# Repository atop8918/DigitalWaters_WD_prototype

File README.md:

# DigitalWaters_WD_prototype
Simplified Schematic for prototype release

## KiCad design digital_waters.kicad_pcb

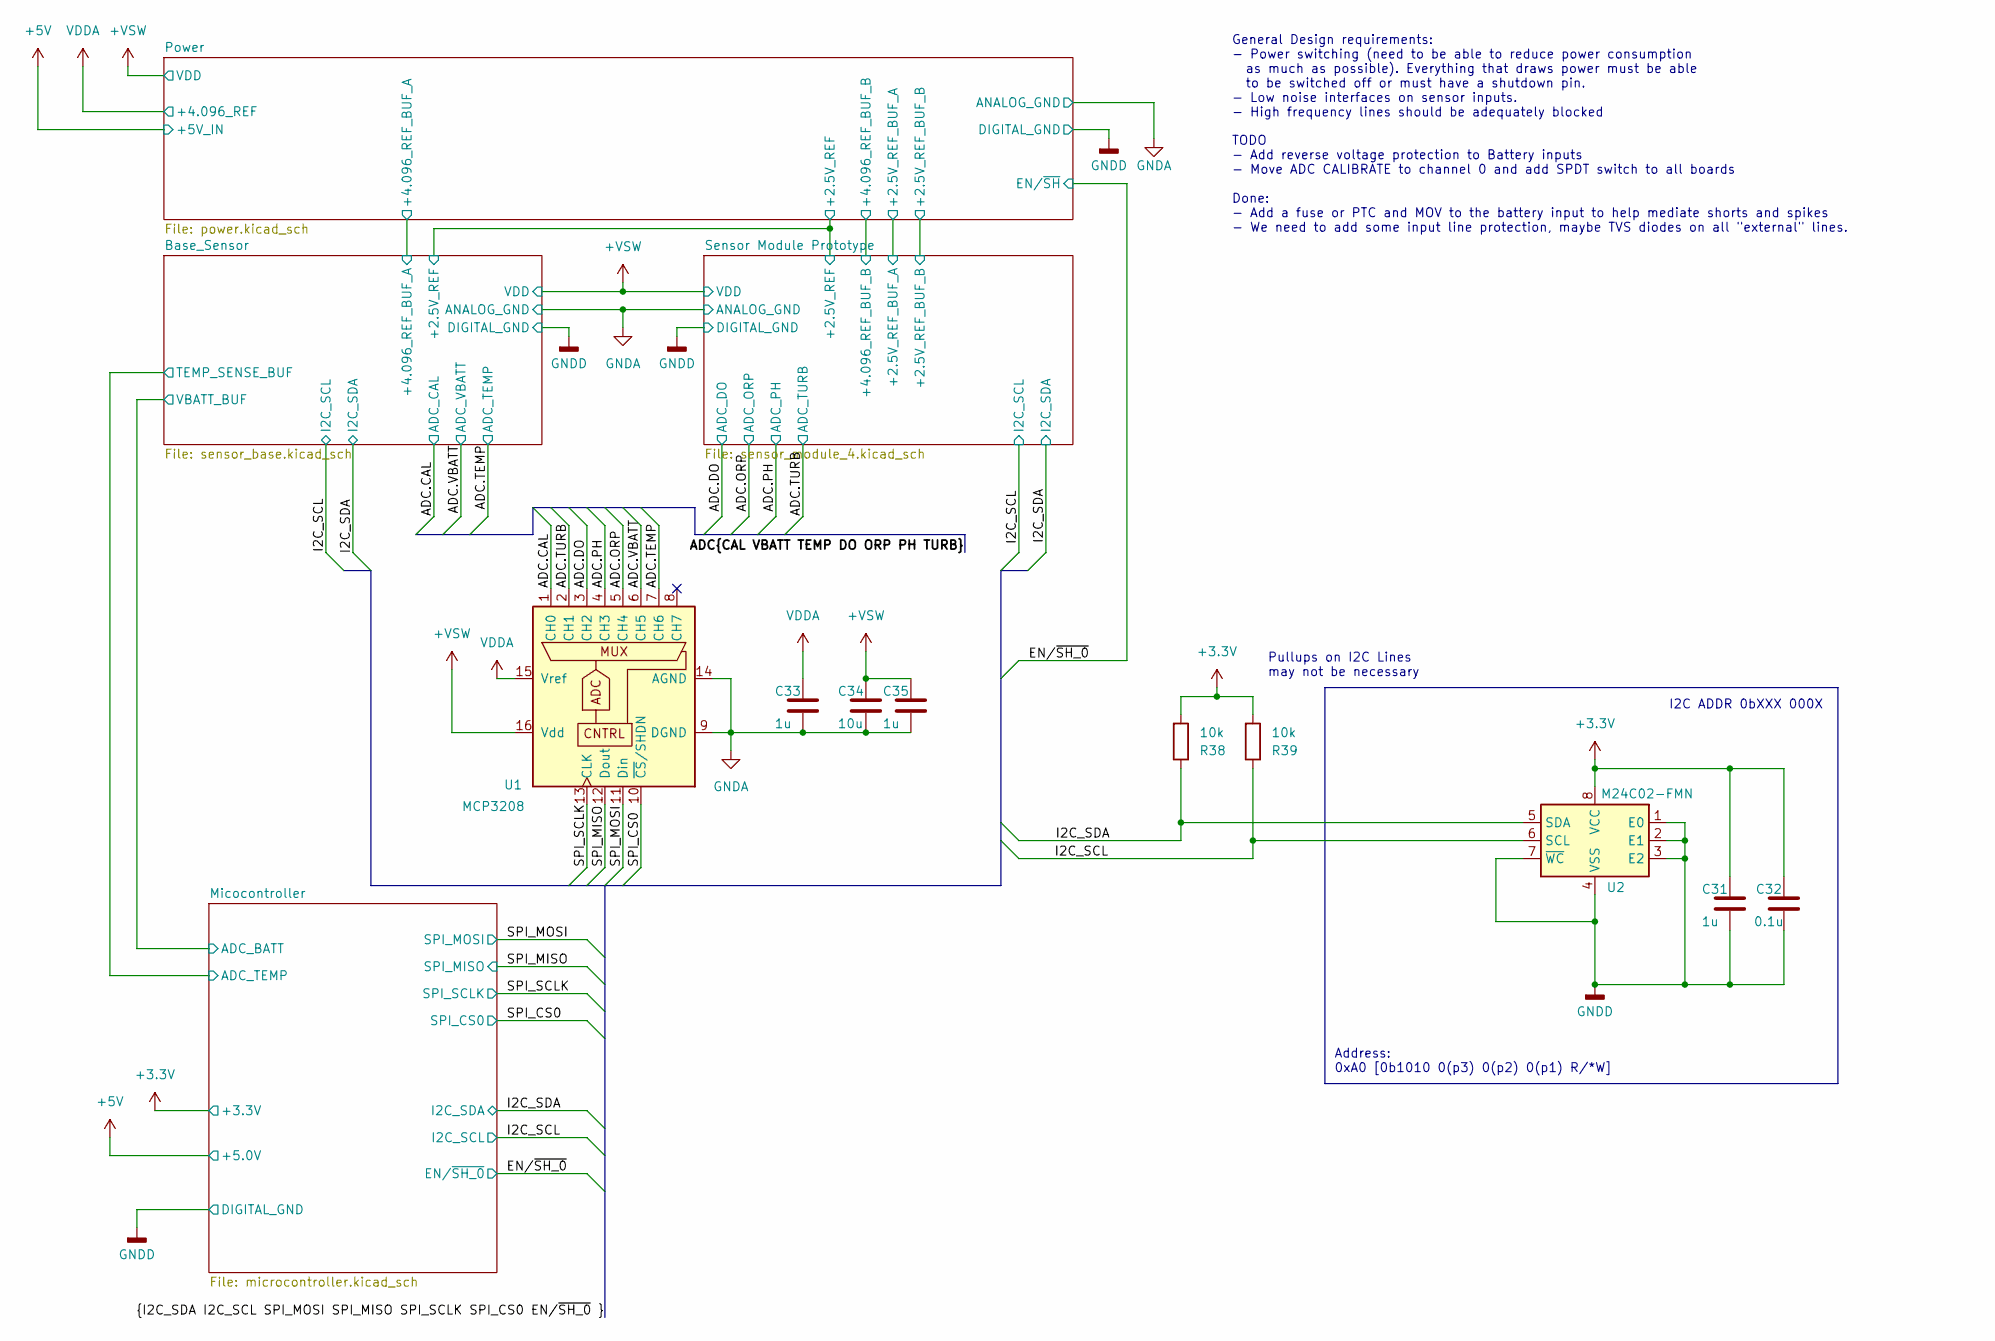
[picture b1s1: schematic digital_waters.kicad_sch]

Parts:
C31, C33, C35: 1u; C_1210_3225Metric_Pad1.33x2.70mm_HandSolder
C32: 0.1u; C_1210_3225Metric_Pad1.33x2.70mm_HandSolder
C34: 10u; C_1210_3225Metric_Pad1.33x2.70mm_HandSolder
R38, R39: 10k; R_1210_3225Metric_Pad1.30x2.65mm_HandSolder
U1: MCP3208; SOIC-16_3.9x9.9mm_P1.27mm
U2: M24C02-FMN; SOIC-8_3.9x4.9mm_P1.27mm

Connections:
+3.3V: C31.1, C32.1, R38.2, R39.2, U2.8 (VCC); also elsewhere on the board
+VSW: C34.1, C35.1, U1.16 (Vdd); also elsewhere on the board
/ADC.CAL: U1.1 (CH0); also elsewhere on the board
/ADC.DO: U1.3 (CH2); also elsewhere on the board
/ADC.ORP: U1.5 (CH4); also elsewhere on the board
/ADC.PH: U1.4 (CH3); also elsewhere on the board
/ADC.TEMP: U1.7 (CH6); also elsewhere on the board
/ADC.TURB: U1.2 (CH1); also elsewhere on the board
/ADC.VBATT: U1.6 (CH5); also elsewhere on the board
/I2C_SCL: R39.1, U2.6 (SCL); also elsewhere on the board
/I2C_SDA: R38.1, U2.5 (SDA); also elsewhere on the board
/SPI_CS0: U1.10 (~CS/SHDN); also elsewhere on the board
/SPI_MISO: U1.12 (Dout); also elsewhere on the board
/SPI_MOSI: U1.11 (Din); also elsewhere on the board
/SPI_SCLK: U1.13 (CLK); also elsewhere on the board
GNDA: C33.2, C34.2, C35.2, U1.9 (DGND), U1.14 (AGND); also elsewhere on the board
GNDD: C31.2, C32.2, U2.1 (E0), U2.2 (E1), U2.3 (E2), U2.4 (VSS), U2.7 (~WC); also elsewhere on the board
VDDA: C33.1, U1.15 (Vref); also elsewhere on the board

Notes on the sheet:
I2C ADDR 0bXXX 000X
Address: 0xA0 [0b1010 0(p3) 0(p2) 0(p1) R/*W]
TODO - Add reverse voltage protection to Battery inputs - Move ADC CALIBRATE to channel 0 and add SPDT switch to all boards Done: - Add a fuse or PTC and MOV to the battery input to help mediate shorts and spikes - We need to add some input line protection, maybe TVS diodes on all "external" lines.
Pullups on I2C Lines may not be necessary
General Design requirements: - Power switching (need to be able to reduce power consumption as much as possible). Everything that draws power must be able to be switched off or must have a shutdown pin. - Low noise interfaces on sensor inputs. - High frequency lines should be adequately blocked

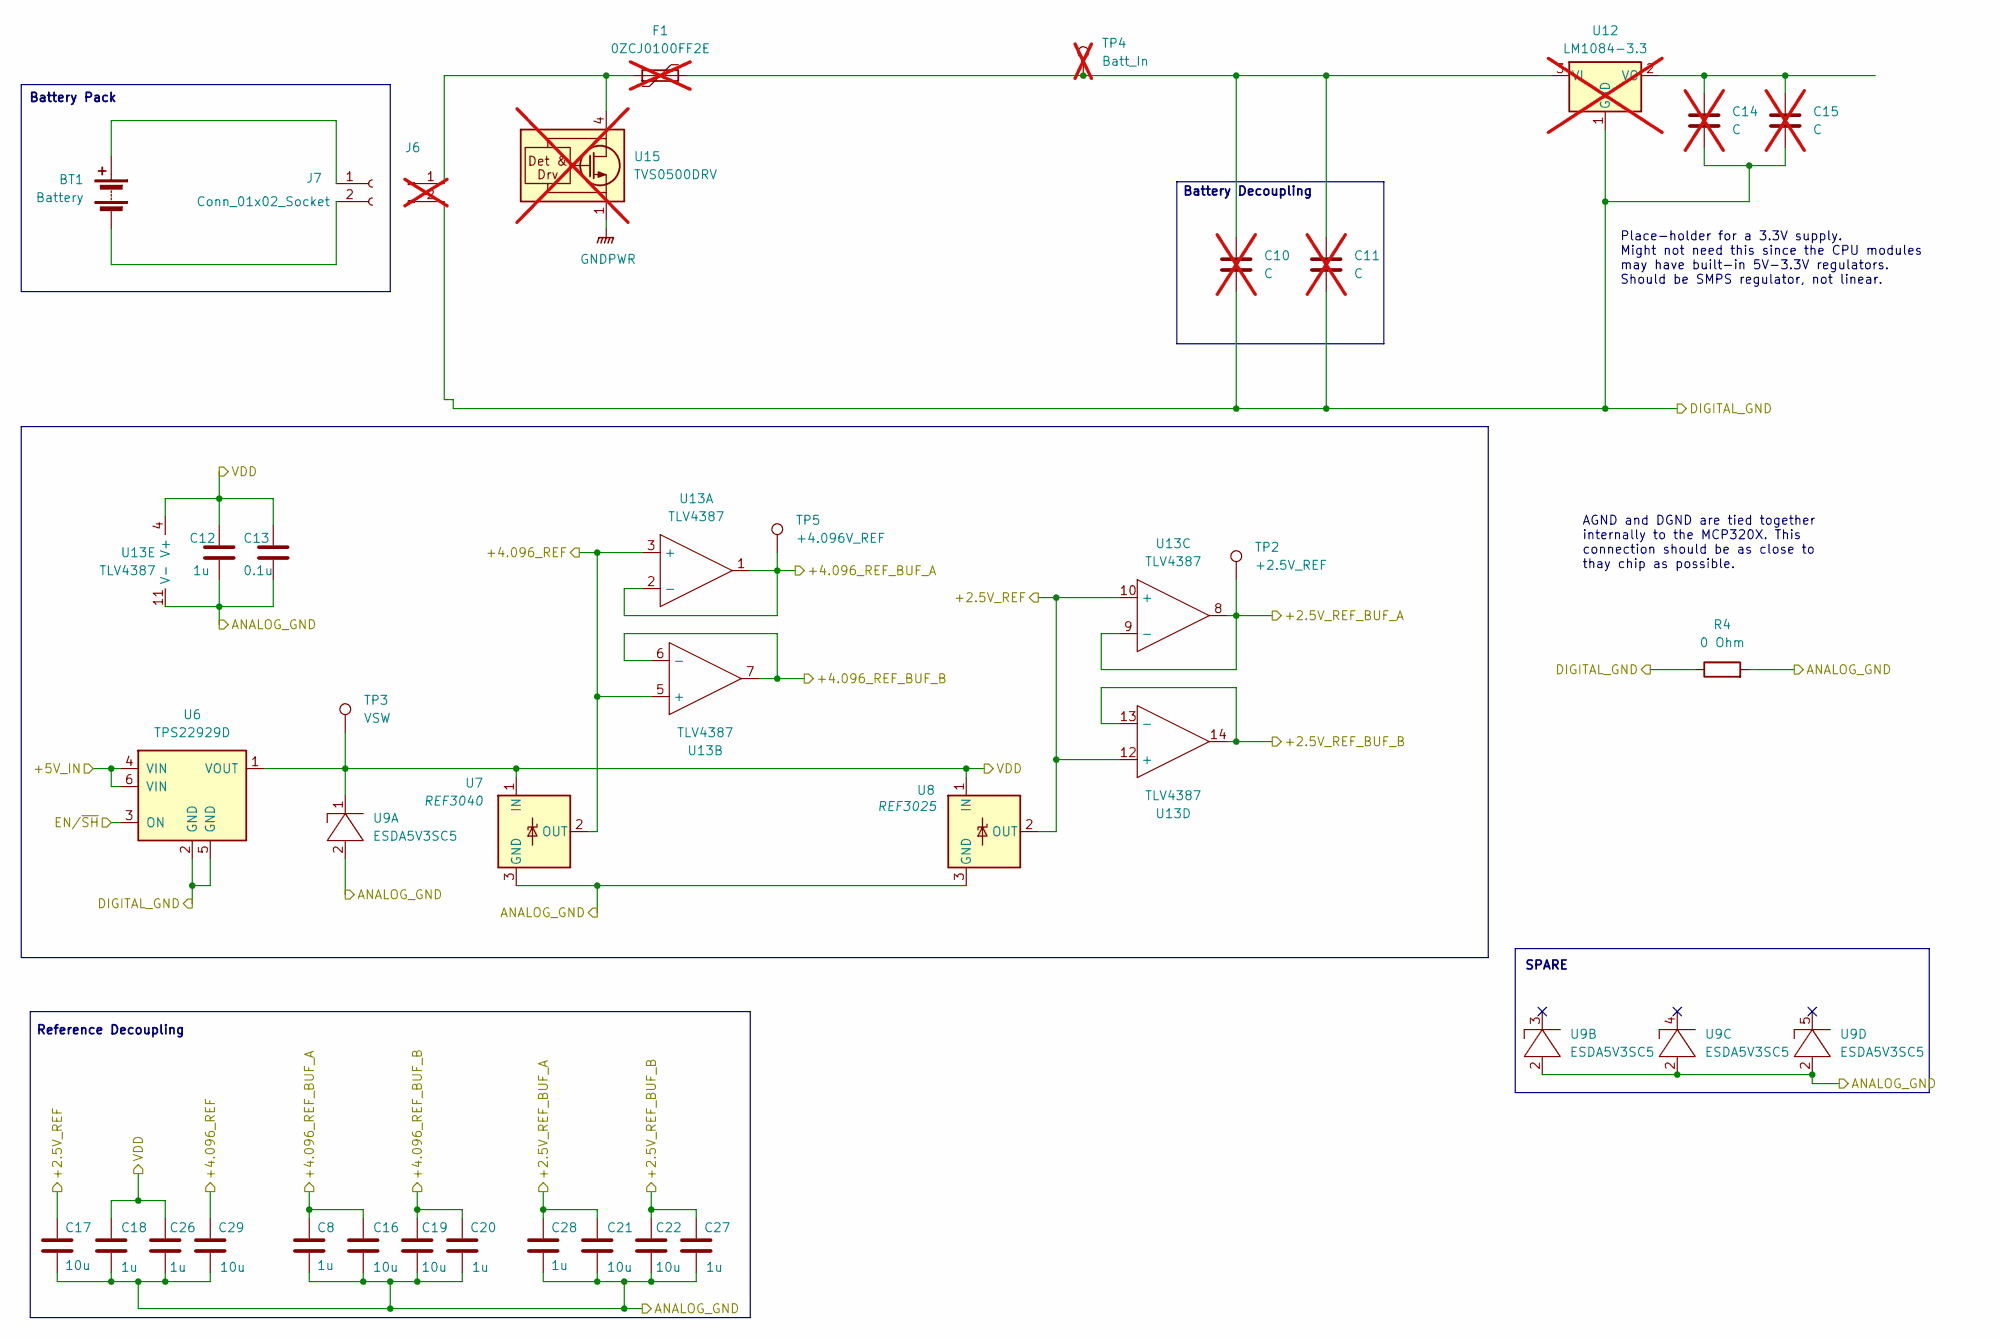
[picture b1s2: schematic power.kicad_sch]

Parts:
BT1: Battery
C8, C12, C18, C20, C26, C27, C28: 1u; C_1210_3225Metric_Pad1.33x2.70mm_HandSolder
C10, C11, C14, C15: C; C_1210_3225Metric_Pad1.33x2.70mm_HandSolder; not fitted
C13: 0.1u; C_1210_3225Metric_Pad1.33x2.70mm_HandSolder
C16, C17, C19, C21, C22, C29: 10u; C_1210_3225Metric_Pad1.33x2.70mm_HandSolder
F1: 0ZCJ0100FF2E; Fuse_1206_3216Metric_Pad1.42x1.75mm_HandSolder; not fitted
J6: Battery In; PinHeader_1x02_P2.54mm_Vertical_SMD_Pin1Left; not fitted
J7: Conn_01x02_Socket
R4: 0 Ohm; R_1210_3225Metric_Pad1.30x2.65mm_HandSolder
TP2: +2.5V_REF; TestPoint_Pad_D3.0mm
TP3: VSW; TestPoint_Pad_D3.0mm
TP4: Batt_In; TestPoint_Pad_D3.0mm; not fitted
TP5: +4.096V_REF; TestPoint_Pad_D3.0mm
U6: TPS22929D; SOT-23-6
U7: REF3040; SOT-23
U8: REF3025; SOT-23
U9: ESDA5V3SC5; SOT-23-5
U12: LM1084-3.3; PinHeader_2x10_P2.54mm_Vertical_SMD; not fitted
U13: TLV4387; TSSOP-14_4.4x5mm_P0.65mm
U15: TVS0500DRV; WSON-6-1EP_2x2mm_P0.65mm_EP1x1.6mm; not fitted

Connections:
+5V: U6.4 (VIN), U6.6 (VIN); also elsewhere on the board
+VSW: C12.1, C13.1, C18.1, C26.1, TP3.1, U6.1 (VOUT), U7.1 (IN), U8.1 (IN), U9.1, U13.4 (V+); also elsewhere on the board
/Base_Sensor/+2.5V_REF: C17.1, U8.2 (OUT), U13.10 (+), U13.12 (+); also elsewhere on the board
/Base_Sensor/+4.096_REF_BUF_A: C8.1, C16.1, TP5.1, U13.1, U13.2 (-); also elsewhere on the board
/EN/~SH_0: U6.3 (ON); also elsewhere on the board
/Power/+2.5V_REF_BUF_A: C21.1, C28.1, TP2.1, U13.8, U13.9 (-); also elsewhere on the board
/Power/+2.5V_REF_BUF_B: C22.1, C27.1, U13.13 (-), U13.14; also elsewhere on the board
/Power/+4.096_REF_BUF_B: C19.1, C20.1, U13.6 (-), U13.7; also elsewhere on the board
GNDA: C8.2, C12.2, C13.2, C16.2, C17.2, C18.2, C19.2, C20.2, C21.2, C22.2, C26.2, C27.2, C28.2, C29.2, R4.2, U7.3 (GND), U8.3 (GND), U9.2, U13.11 (V-); also elsewhere on the board
GNDD: C10.2, C11.2, C14.2, C15.2, J6.2, R4.1, U6.2 (GND), U6.5 (GND), U12.1 (GND); also elsewhere on the board
unnamed: BT1.1 (+), J7.1
unnamed: BT1.2 (-), J7.2
unnamed: C10.1, C11.1, F1.2, TP4.1, U12.3 (VI)
unnamed: C14.1, C15.1, U12.2 (VO)
unnamed: F1.1, J6.1, U15.4 (IN), U15.5 (IN), U15.6 (IN)
unnamed: U15.1 (GND), U15.2 (GND), U15.3 (GND), U15.7 (GND)
VDDA: C29.1, U7.2 (OUT), U13.3 (+), U13.5 (+); also elsewhere on the board

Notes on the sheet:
Battery Pack
Place-holder for a 3.3V supply. Might not need this since the CPU modules may have built-in 5V-3.3V regulators. Should be SMPS regulator, not linear.
Battery Decoupling
AGND and DGND are tied together internally to the MCP320X. This connection should be as close to thay chip as possible.
SPARE
Reference Decoupling

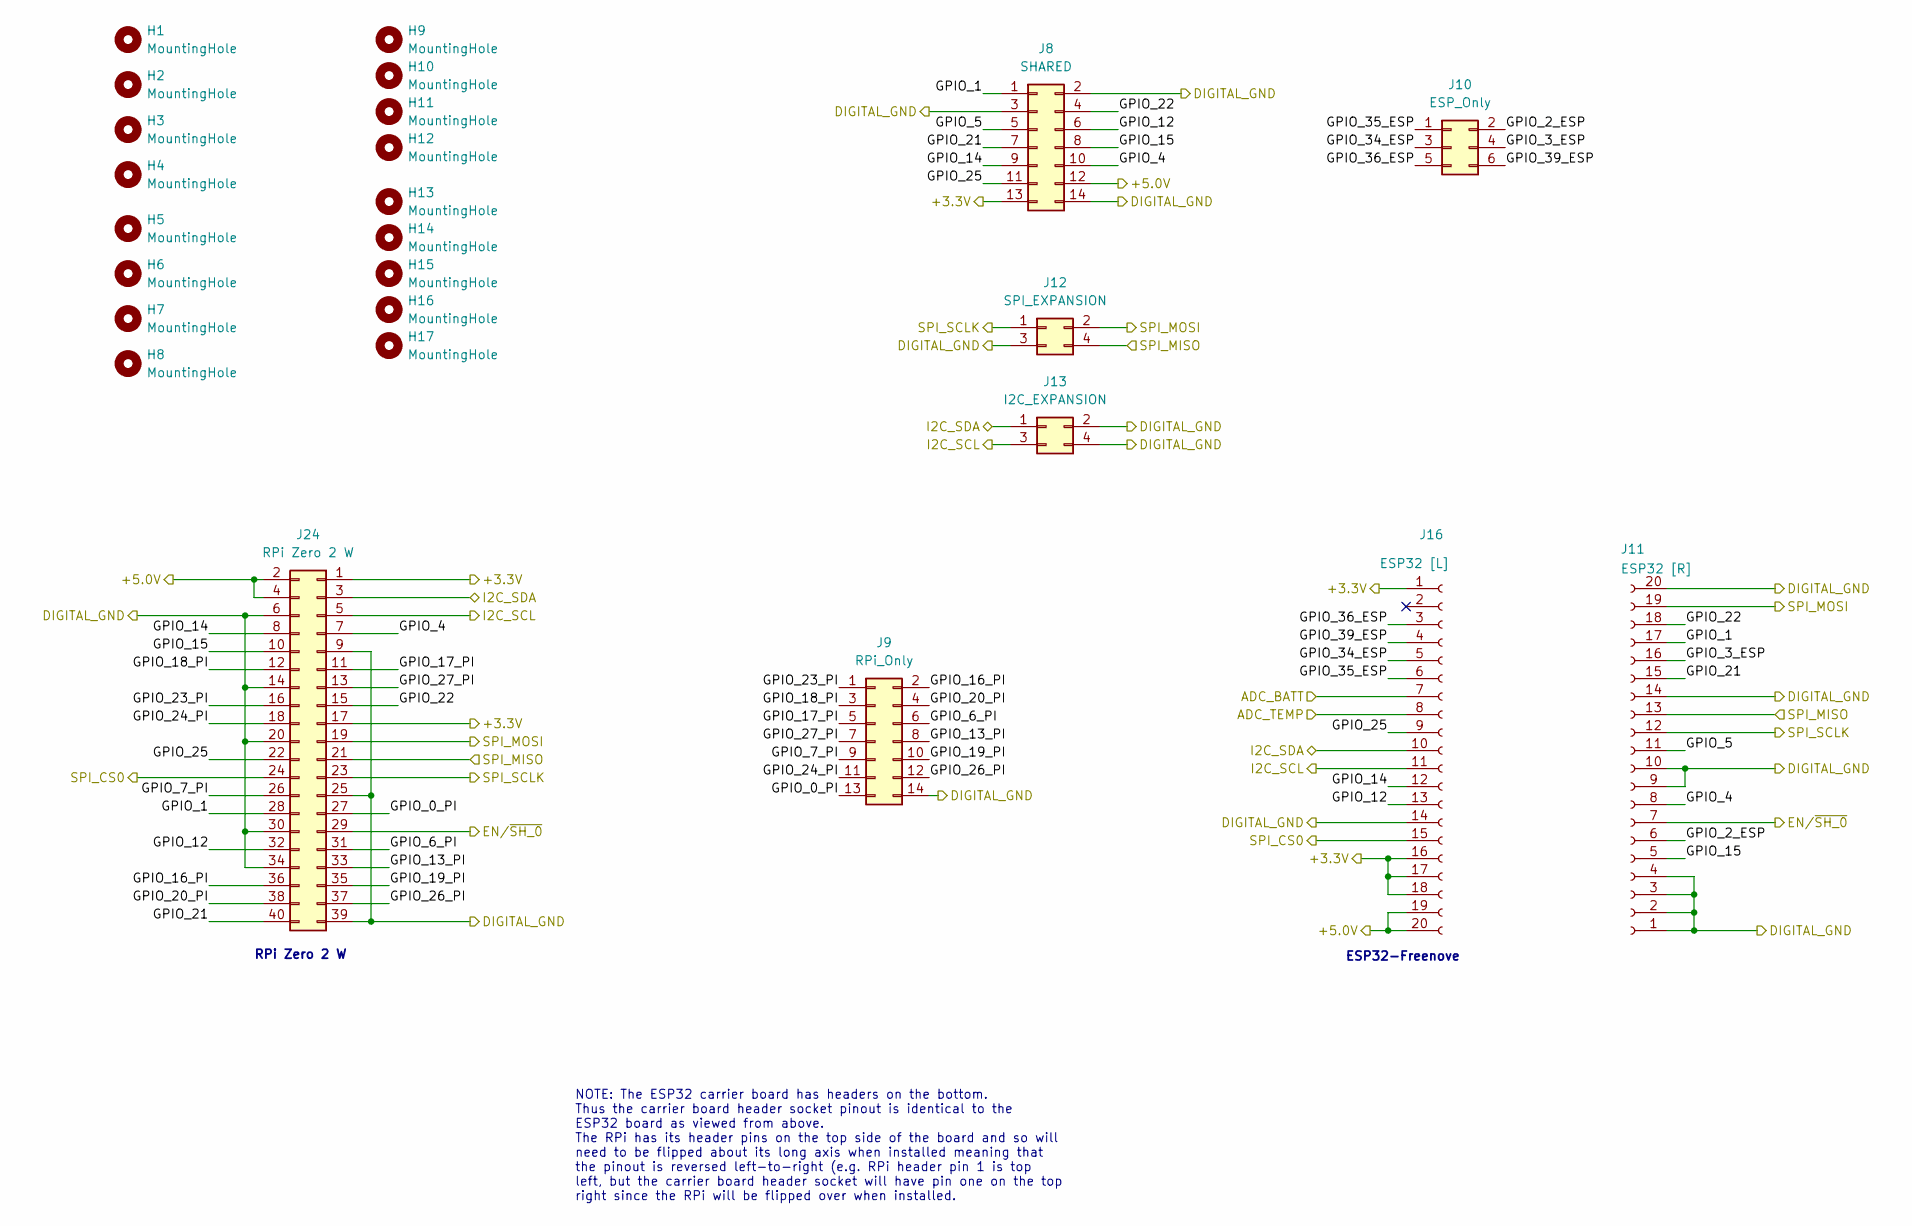
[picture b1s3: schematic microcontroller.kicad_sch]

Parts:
H1, H2, H3, H4, H5, H6, H7, H8, H9, H10, H11, H12, H13, H14, H15, H16, H17: MountingHole; MountingHole_2.7mm_M2.5_ISO14580
J8: SHARED; PinHeader_2x07_P2.54mm_Vertical_SMD
J9: RPi_Only; PinHeader_2x07_P2.54mm_Vertical_SMD
J10: ESP_Only; PinHeader_2x03_P2.54mm_Vertical_SMD
J11: ESP32 [R]; PinSocket_1x20_P2.54mm_Vertical_SMD_Pin1Left
J12: SPI_EXPANSION; PinHeader_2x02_P2.54mm_Vertical_SMD
J13: I2C_EXPANSION; PinHeader_2x02_P2.54mm_Vertical_SMD
J16: ESP32 [L]; PinSocket_1x20_P2.54mm_Vertical_SMD_Pin1Left
J24: RPi Zero 2 W; PinSocket_2x20_P2.54mm_Vertical_SMD

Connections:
+3.3V: J8.13, J16.1, J16.16, J16.17, J16.18, J24.1, J24.17; also elsewhere on the board
+5V: J8.12, J16.19, J16.20, J24.2, J24.4; also elsewhere on the board
/Base_Sensor/TEMP_SENSE_BUF: J16.8; also elsewhere on the board
/Base_Sensor/VBATT_BUF: J16.7; also elsewhere on the board
/EN/~SH_0: J11.7, J24.29; also elsewhere on the board
/I2C_SCL: J13.3, J16.11, J24.5; also elsewhere on the board
/I2C_SDA: J13.1, J16.10, J24.3; also elsewhere on the board
/Micocontroller/GPIO_0_PI: J9.13, J24.27
/Micocontroller/GPIO_1: J8.1, J11.17, J24.28
/Micocontroller/GPIO_2_ESP: J10.2, J11.6
/Micocontroller/GPIO_3_ESP: J10.4, J11.16
/Micocontroller/GPIO_4: J8.10, J11.8, J24.7
/Micocontroller/GPIO_5: J8.5, J11.11
/Micocontroller/GPIO_6_PI: J9.6, J24.31
/Micocontroller/GPIO_7_PI: J9.9, J24.26
/Micocontroller/GPIO_12: J8.6, J16.13, J24.32
/Micocontroller/GPIO_13_PI: J9.8, J24.33
/Micocontroller/GPIO_14: J8.9, J16.12, J24.8
/Micocontroller/GPIO_15: J8.8, J11.5, J24.10
/Micocontroller/GPIO_16_PI: J9.2, J24.36
/Micocontroller/GPIO_17_PI: J9.5, J24.11
/Micocontroller/GPIO_18_PI: J9.3, J24.12
/Micocontroller/GPIO_19_PI: J9.10, J24.35
/Micocontroller/GPIO_20_PI: J9.4, J24.38
/Micocontroller/GPIO_21: J8.7, J11.15, J24.40
/Micocontroller/GPIO_22: J8.4, J11.18, J24.15
/Micocontroller/GPIO_23_PI: J9.1, J24.16
/Micocontroller/GPIO_24_PI: J9.11, J24.18
/Micocontroller/GPIO_25: J8.11, J16.9, J24.22
/Micocontroller/GPIO_26_PI: J9.12, J24.37
/Micocontroller/GPIO_27_PI: J9.7, J24.13
/Micocontroller/GPIO_34_ESP: J10.3, J16.5
/Micocontroller/GPIO_35_ESP: J10.1, J16.6
/Micocontroller/GPIO_36_ESP: J10.5, J16.3
/Micocontroller/GPIO_39_ESP: J10.6, J16.4
/SPI_CS0: J16.15, J24.24; also elsewhere on the board
/SPI_MISO: J11.13, J12.4, J24.21; also elsewhere on the board
/SPI_MOSI: J11.19, J12.2, J24.19; also elsewhere on the board
/SPI_SCLK: J11.12, J12.1, J24.23; also elsewhere on the board
GNDD: J8.2, J8.3, J8.14, J9.14, J11.1, J11.2, J11.3, J11.4, J11.9, J11.10, J11.14, J11.20, J12.3, J13.2, J13.4, J16.14, J24.6, J24.9, J24.14, J24.20, J24.25, J24.30, J24.34, J24.39; also elsewhere on the board

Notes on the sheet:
ESP32-Freenove
RPi Zero 2 W
NOTE: The ESP32 carrier board has headers on the bottom. Thus the carrier board header socket pinout is identical to the ESP32 board as viewed from above. The RPi has its header pins on the top side of the board and so will need to be flipped about its long axis when installed meaning that the pino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

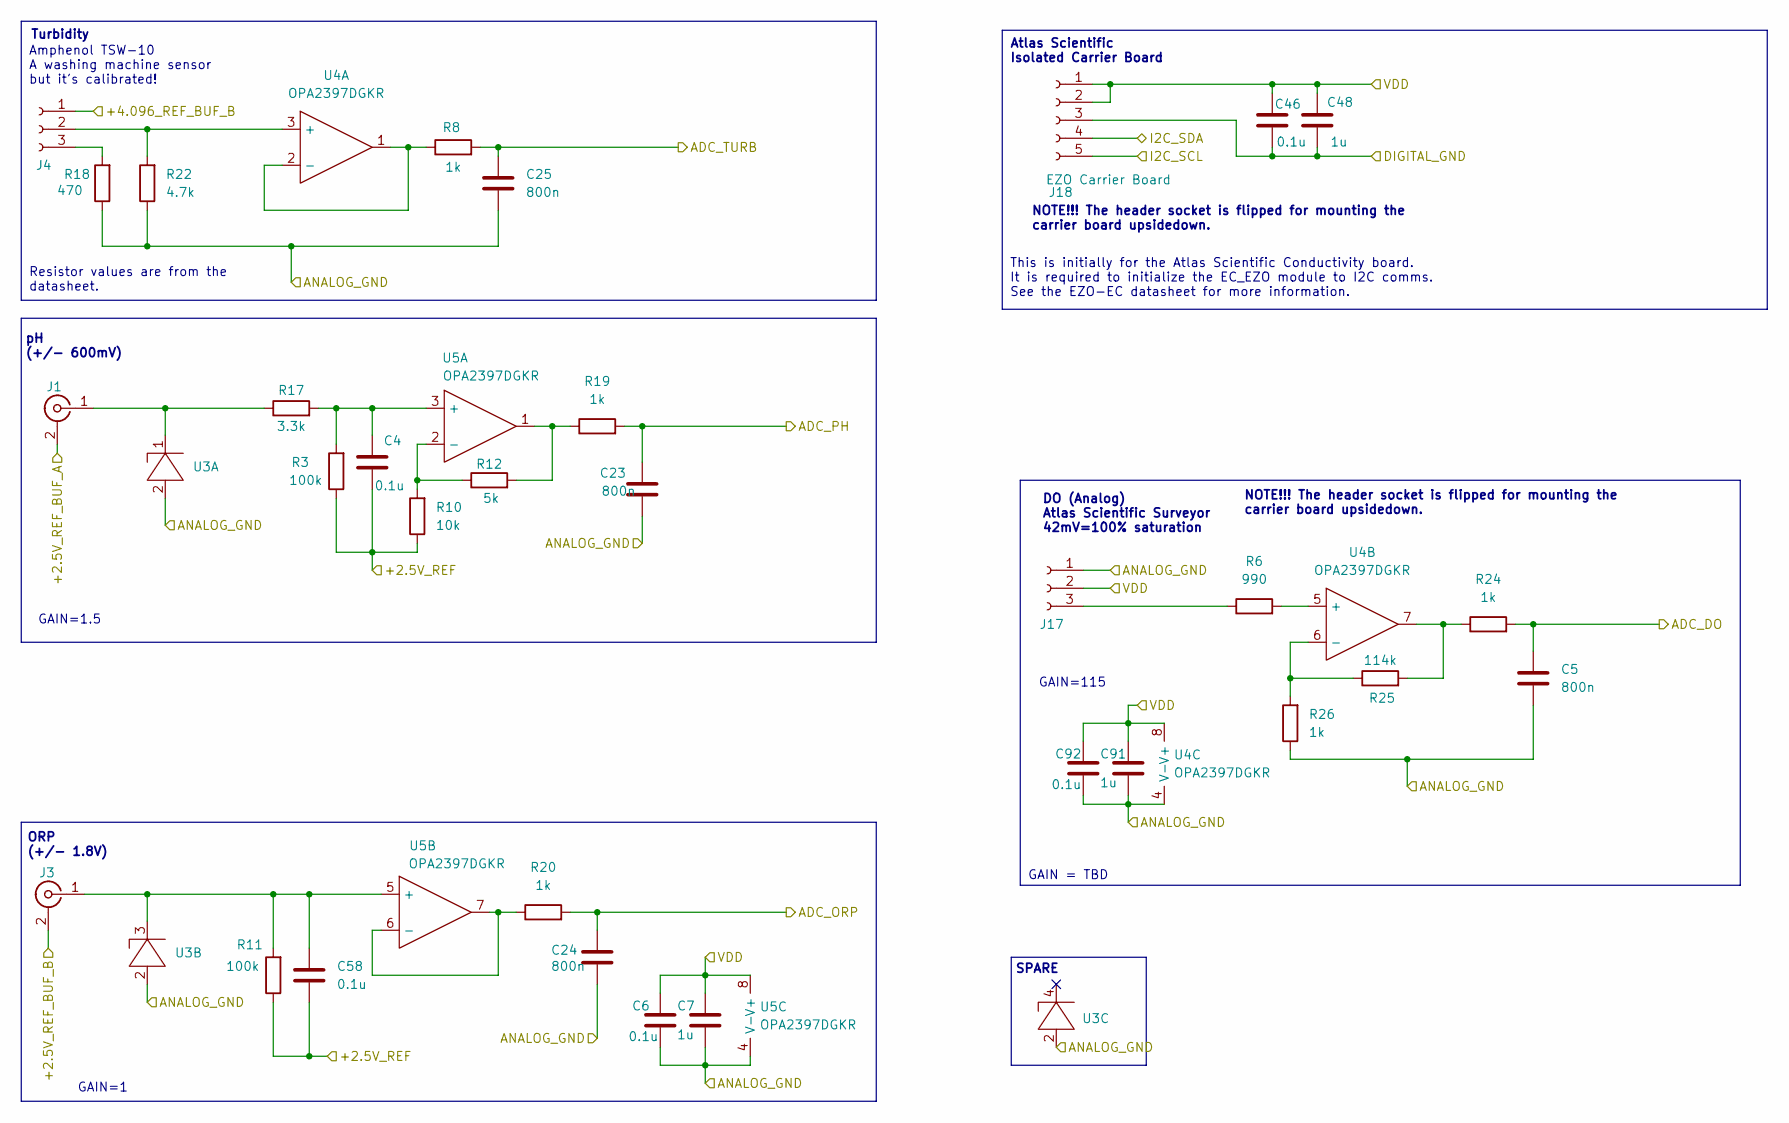
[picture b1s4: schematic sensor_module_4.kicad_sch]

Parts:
C4, C6, C46, C58, C92: 0.1u; C_1210_3225Metric_Pad1.33x2.70mm_HandSolder
C5, C23, C24, C25: 800n; C_1210_3225Metric_Pad1.33x2.70mm_HandSolder
C7, C48, C91: 1u; C_1210_3225Metric_Pad1.33x2.70mm_HandSolder
J1: pH_IN; PinHeader_1x02_P2.54mm_Vertical_SMD_Pin1Left
J3: ORP_In; PinHeader_1x02_P2.54mm_Vertical_SMD_Pin1Left
J4: Turbidity TSW-10; PinHeader_1x03_P2.54mm_Vertical_SMD_Pin1Left
J17: Atlas Surveyor; PinSocket_1x03_P2.54mm_Vertical
J18: EZO Carrier Board; PinSocket_1x05_P2.54mm_Vertical
R3, R11: 100k; R_1210_3225Metric_Pad1.30x2.65mm_HandSolder
R6: 990; R_1210_3225Metric_Pad1.30x2.65mm_HandSolder
R8, R19, R20, R24, R26: 1k; R_1210_3225Metric_Pad1.30x2.65mm_HandSolder
R10: 10k; R_1210_3225Metric_Pad1.30x2.65mm_HandSolder
R12: 5k; R_1210_3225Metric_Pad1.30x2.65mm_HandSolder
R17: 3.3k; R_1210_3225Metric_Pad1.30x2.65mm_HandSolder
R18: 470; R_1210_3225Metric_Pad1.30x2.65mm_HandSolder
R22: 4.7k; R_1210_3225Metric_Pad1.30x2.65mm_HandSolder
R25: 114k; R_1210_3225Metric_Pad1.30x2.65mm_HandSolder
U3: ESDA5V3SC5; SOT-23-5
U4, U5: OPA2397DGKR; SOIC-8_3.9x4.9mm_P1.27mm

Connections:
+VSW: C6.1, C7.1, C46.1, C48.1, C91.1, C92.1, J17.2, J18.1, J18.2, U4.8 (V+), U5.8 (V+); also elsewhere on the board
/ADC.DO: C5.1, R24.2; also elsewhere on the board
/ADC.ORP: C24.1, R20.2; also elsewhere on the board
/ADC.PH: C23.1, R19.2; also elsewhere on the board
/ADC.TURB: C25.1, R8.2; also elsewhere on the board
/Base_Sensor/+2.5V_REF: C4.2, C58.2, R3.1, R10.1, R11.1; also elsewhere on the board
/I2C_SCL: J18.5; also elsewhere on the board
/I2C_SDA: J18.4; also elsewhere on the board
/Power/+2.5V_REF_BUF_A: J1.2 (Ext); also elsewhere on the board
/Power/+2.5V_REF_BUF_B: J3.2 (Ext); also elsewhere on the board
/Power/+4.096_REF_BUF_B: J4.1; also elsewhere on the board
GNDA: C5.2, C6.2, C7.2, C23.2, C24.2, C25.2, C91.2, C92.2, J17.1, R18.1, R22.1, R26.1, U3.2, U4.4 (V-), U5.4 (V-); also elsewhere on the board
GNDD: C46.2, C48.2, J18.3; also elsewhere on the board
unnamed: J1.1 (In), R17.1, U3.1
unnamed: C58.1, J3.1 (In), R11.2, U3.3, U5.5 (+)
unnamed: J4.2, R22.2, U4.3 (+)
unnamed: J4.3, R18.2
unnamed: J17.3, R6.1
unnamed: R12.2, R19.1, U5.1
unnamed: R24.1, R25.2, U4.7
unnamed: R8.1, U4.1, U4.2 (-)
unnamed: R6.2, U4.5 (+)
unnamed: R25.1, R26.2, U4.6 (-)
unnamed: C4.1, R3.2, R17.2, U5.3 (+)
unnamed: R10.2, R12.1, U5.2 (-)
unnamed: R20.1, U5.6 (-), U5.7

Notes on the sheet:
Atlas Scientific Isolated Carrier Board
Turbidity
NOTE!!! The header socket is flipped for mounting the carrier board upsidedown.
Amphenol TSW-10 A washing machine sensor but it's calibrated!
GAIN=1.5
GAIN=1
Resistor values are from the datasheet.
ORP (+/- 1.8V)
pH (+/- 600mV)
GAIN = TBD
DO (Analog) Atlas Scientific Surveyor 42mV=100% saturation
This is initially for the Atlas Scientific Conductivity board. It is required to initialize the EC_EZO module to I2C comms. See the EZO-EC datasheet for more information.
SPARE
GAIN=115

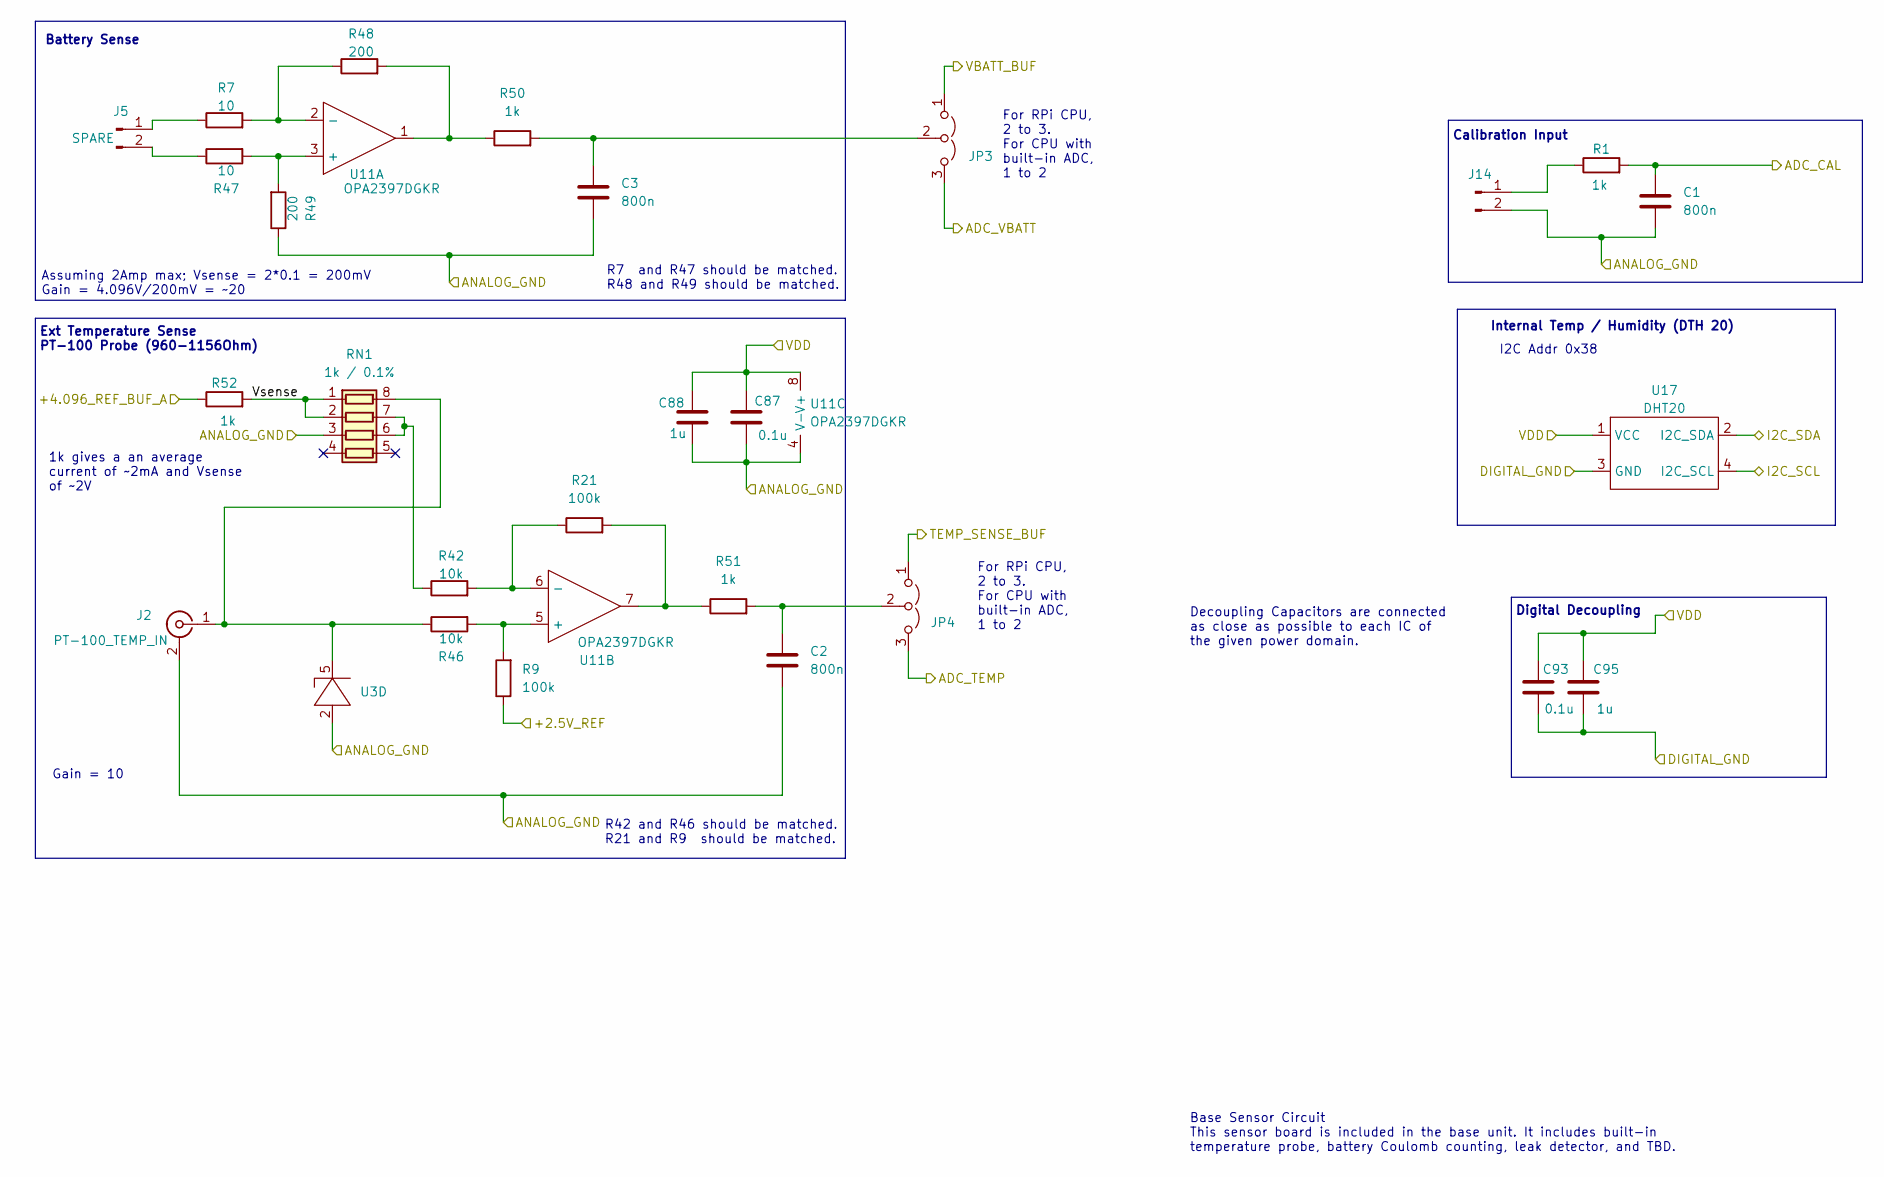
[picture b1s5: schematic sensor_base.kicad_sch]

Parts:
C1, C2, C3: 800n; C_1210_3225Metric_Pad1.33x2.70mm_HandSolder
C87, C93: 0.1u; C_1210_3225Metric_Pad1.33x2.70mm_HandSolder
C88, C95: 1u; C_1210_3225Metric_Pad1.33x2.70mm_HandSolder
J2: PT-100_TEMP_IN; PinHeader_1x02_P2.54mm_Vertical_SMD_Pin1Left
J5: SPARE; PinHeader_1x02_P2.54mm_Vertical_SMD_Pin1Left
J14: Calibration_In; PinHeader_1x02_P2.54mm_Vertical_SMD_Pin1Left
JP3: RPi_Batt; PinHeader_1x03_P2.54mm_Vertical_SMD_Pin1Left
JP4: RPi_Temp; PinHeader_1x03_P2.54mm_Vertical_SMD_Pin1Left
R1, R50, R51, R52: 1k; R_1210_3225Metric_Pad1.30x2.65mm_HandSolder
R7, R47: 10; R_1210_3225Metric_Pad1.30x2.65mm_HandSolder
R9, R21: 100k; R_1210_3225Metric_Pad1.30x2.65mm_HandSolder
R42, R46: 10k; R_1210_3225Metric_Pad1.30x2.65mm_HandSolder
R48, R49: 200; R_1210_3225Metric_Pad1.30x2.65mm_HandSolder
RN1: 1k / 0.1%; R_Array_Concave_4x0603
U3: ESDA5V3SC5; SOT-23-5
U11: OPA2397DGKR; SOIC-8_3.9x4.9mm_P1.27mm
U17: DHT20; PinSocket_1x04_P2.54mm_Vertical_SMD_Pin1Left

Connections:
+VSW: C87.1, C88.1, C93.1, C95.1, U11.8 (V+), U17.1 (VCC); also elsewhere on the board
/ADC.CAL: C1.1, R1.2; also elsewhere on the board
/ADC.TEMP: JP4.3 (B); also elsewhere on the board
/ADC.VBATT: JP3.3 (B); also elsewhere on the board
/Base_Sensor/+2.5V_REF: R9.1; also elsewhere on the board
/Base_Sensor/+4.096_REF_BUF_A: R52.1; also elsewhere on the board
/Base_Sensor/TEMP_SENSE_BUF: JP4.1 (A); also elsewhere on the board
/Base_Sensor/VBATT_BUF: JP3.1 (A); also elsewhere on the board
/Base_Sensor/Vsense: R52.2, RN1.1 (R1.1), RN1.2 (R2.1)
/I2C_SCL: U17.4 (I2C_SCL); also elsewhere on the board
/I2C_SDA: U17.2 (I2C_SDA); also elsewhere on the board
GNDA: C1.2, C2.2, C3.2, C87.2, C88.2, J2.2 (Ext), J14.2, R49.1, RN1.3 (R3.1), U3.2, U11.4 (V-); also elsewhere on the board
GNDD: C93.2, C95.2, U17.3 (GND); also elsewhere on the board
unnamed: J2.1 (In), R46.1, RN1.8 (R1.2), U3.5
unnamed: J5.1, R7.1
unnamed: J5.2, R47.1
unnamed: J14.1, R1.1
unnamed: C3.1, JP3.2 (C), R50.2
unnamed: C2.1, JP4.2 (C), R51.2
unnamed: R21.2, R51.1, U11.7
unnamed: R48.2, R50.1, U11.1
unnamed: R42.1, RN1.6 (R3.2), RN1.7 (R2.2)
unnamed: R47.2, R49.2, U11.3 (+)
unnamed: R7.2, R48.1, U11.2 (-)
unnamed: R9.2, R46.2, U11.5 (+)
unnamed: R21.1, R42.2, U11.6 (-)

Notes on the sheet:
Battery Sense
Decoupling Capacitors are connected as close as possible to each IC of the given power domain.
I2C Addr 0x38
Calibration Input
For RPi CPU, 2 to 3. For CPU with built-in ADC, 1 to 2
Gain = 10
Digital Decoupling
Assuming 2Amp max; Vsense = 2*0.1 = 200mV Gain = 4.096V/200mV = ~20
Base Sensor Circuit This sensor board is included in the base unit. It includes built-in temperature probe, battery Coulomb counting, leak detector, and TBD.
Internal Temp / Humidity (DTH 20)
Ext Temperature Sense PT-100 Probe (960-1156Ohm)
R42 and R46 should be matched. R21 and R9 should be matched.
R7 and R47 should be matched. R48 and R49 should be matched.
1k gives a an average current of ~2mA and Vsense of ~2V

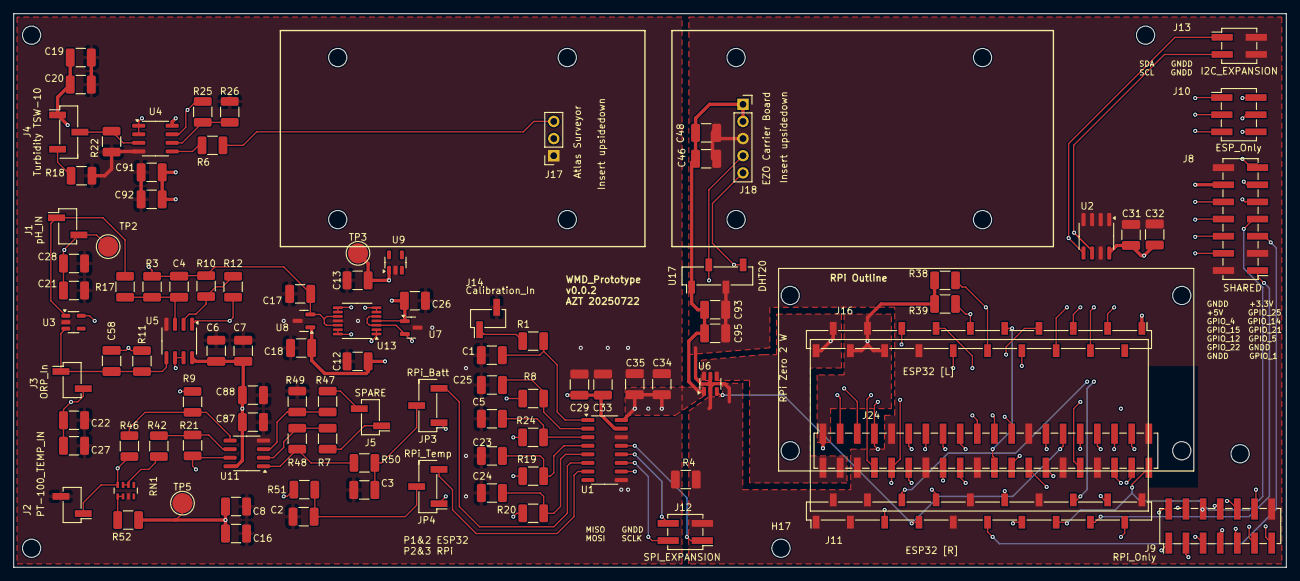
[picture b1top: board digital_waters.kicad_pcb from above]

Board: 4 copper layers, 188.5 x 82.0 mm, 118 parts (0 on the bottom side), 82 nets.

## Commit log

2025-06-19 Inception A little late, but the prototype board and schematic mostly ready for gerbers and manufacturing. Some somponent values still need to be defined but this is a BOM issue, not a board issue.
2025-06-19 Added board mounting holes, basic dimensions, and a board pdf file for casual viewing.
2025-06-19 Added some silkscreen comments. Added a keepout for the ESP32 antenna.
2025-06-19 Forgot to add the board pdf...
2025-06-19 Generated gerbers
2025-07-22 BUG_FIX ------- - Swapped ground for the 2.5V reference on the non-inverting leg of U11B (External temperature probe) This is due to the fact that the temp probe voltage can go both above and below t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
    FEATURES
    --------
    - Finalized many of the parts for the BOM
